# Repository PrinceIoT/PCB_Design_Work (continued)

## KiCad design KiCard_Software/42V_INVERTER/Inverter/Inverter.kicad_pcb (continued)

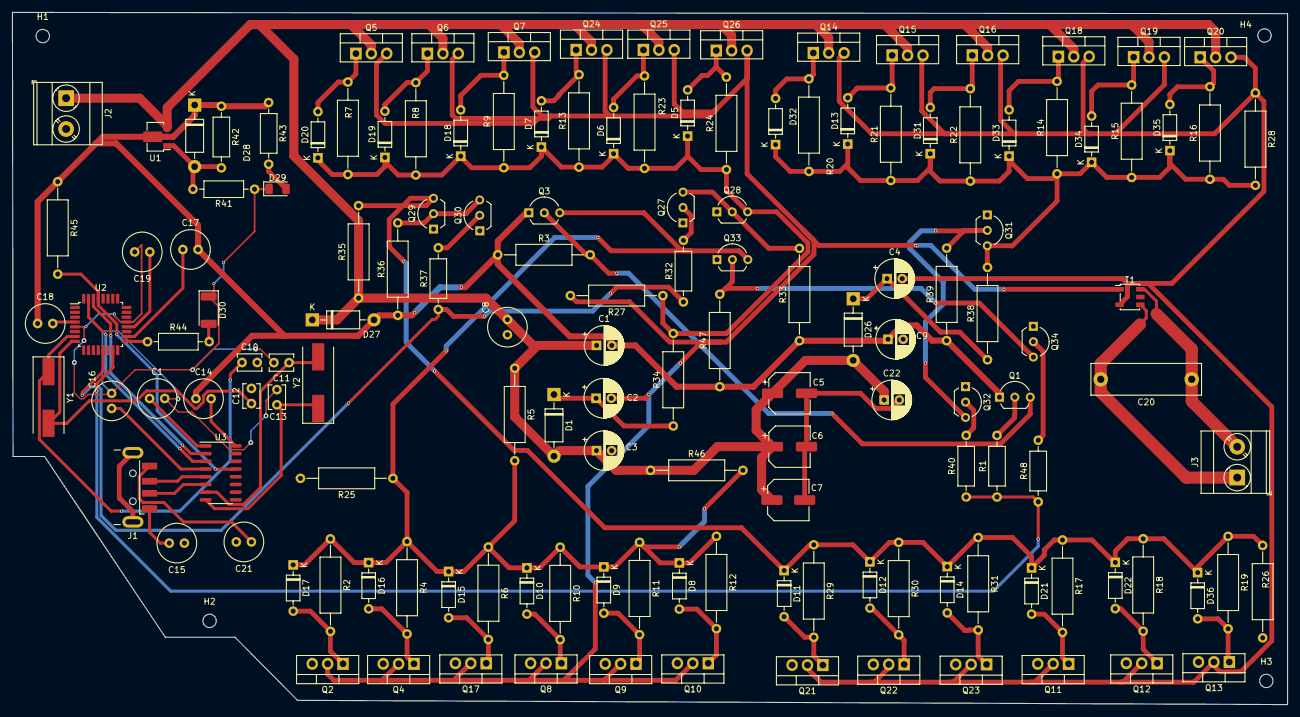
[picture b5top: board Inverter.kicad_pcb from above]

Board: 2 copper layers, 210.2 x 114.1 mm, 148 parts (0 on the bottom side), 70 nets.

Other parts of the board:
C1#2: 0.1uF; C_Radial_D6.3mm_H7.0mm_P2.50mm
Q1, Q3: 2N3904; TO-92_Inline_Wide
R1: 200; R_Axial_DIN0207_L6.3mm_D2.5mm_P10.16mm_Horizontal
R3: 10k; R_Axial_DIN0309_L9.0mm_D3.2mm_P15.24mm_Horizontal
R5: 20k; R_Axial_DIN0309_L9.0mm_D3.2mm_P15.24mm_Horizontal

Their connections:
11: R1.1; also elsewhere on the board
unnamed 9: Q3.3 (C), R5.2; also elsewhere on the board
unnamed: Q1.2 (B), R1.2
unnamed: Q1.3 (C), Q3.2 (B), R3.2

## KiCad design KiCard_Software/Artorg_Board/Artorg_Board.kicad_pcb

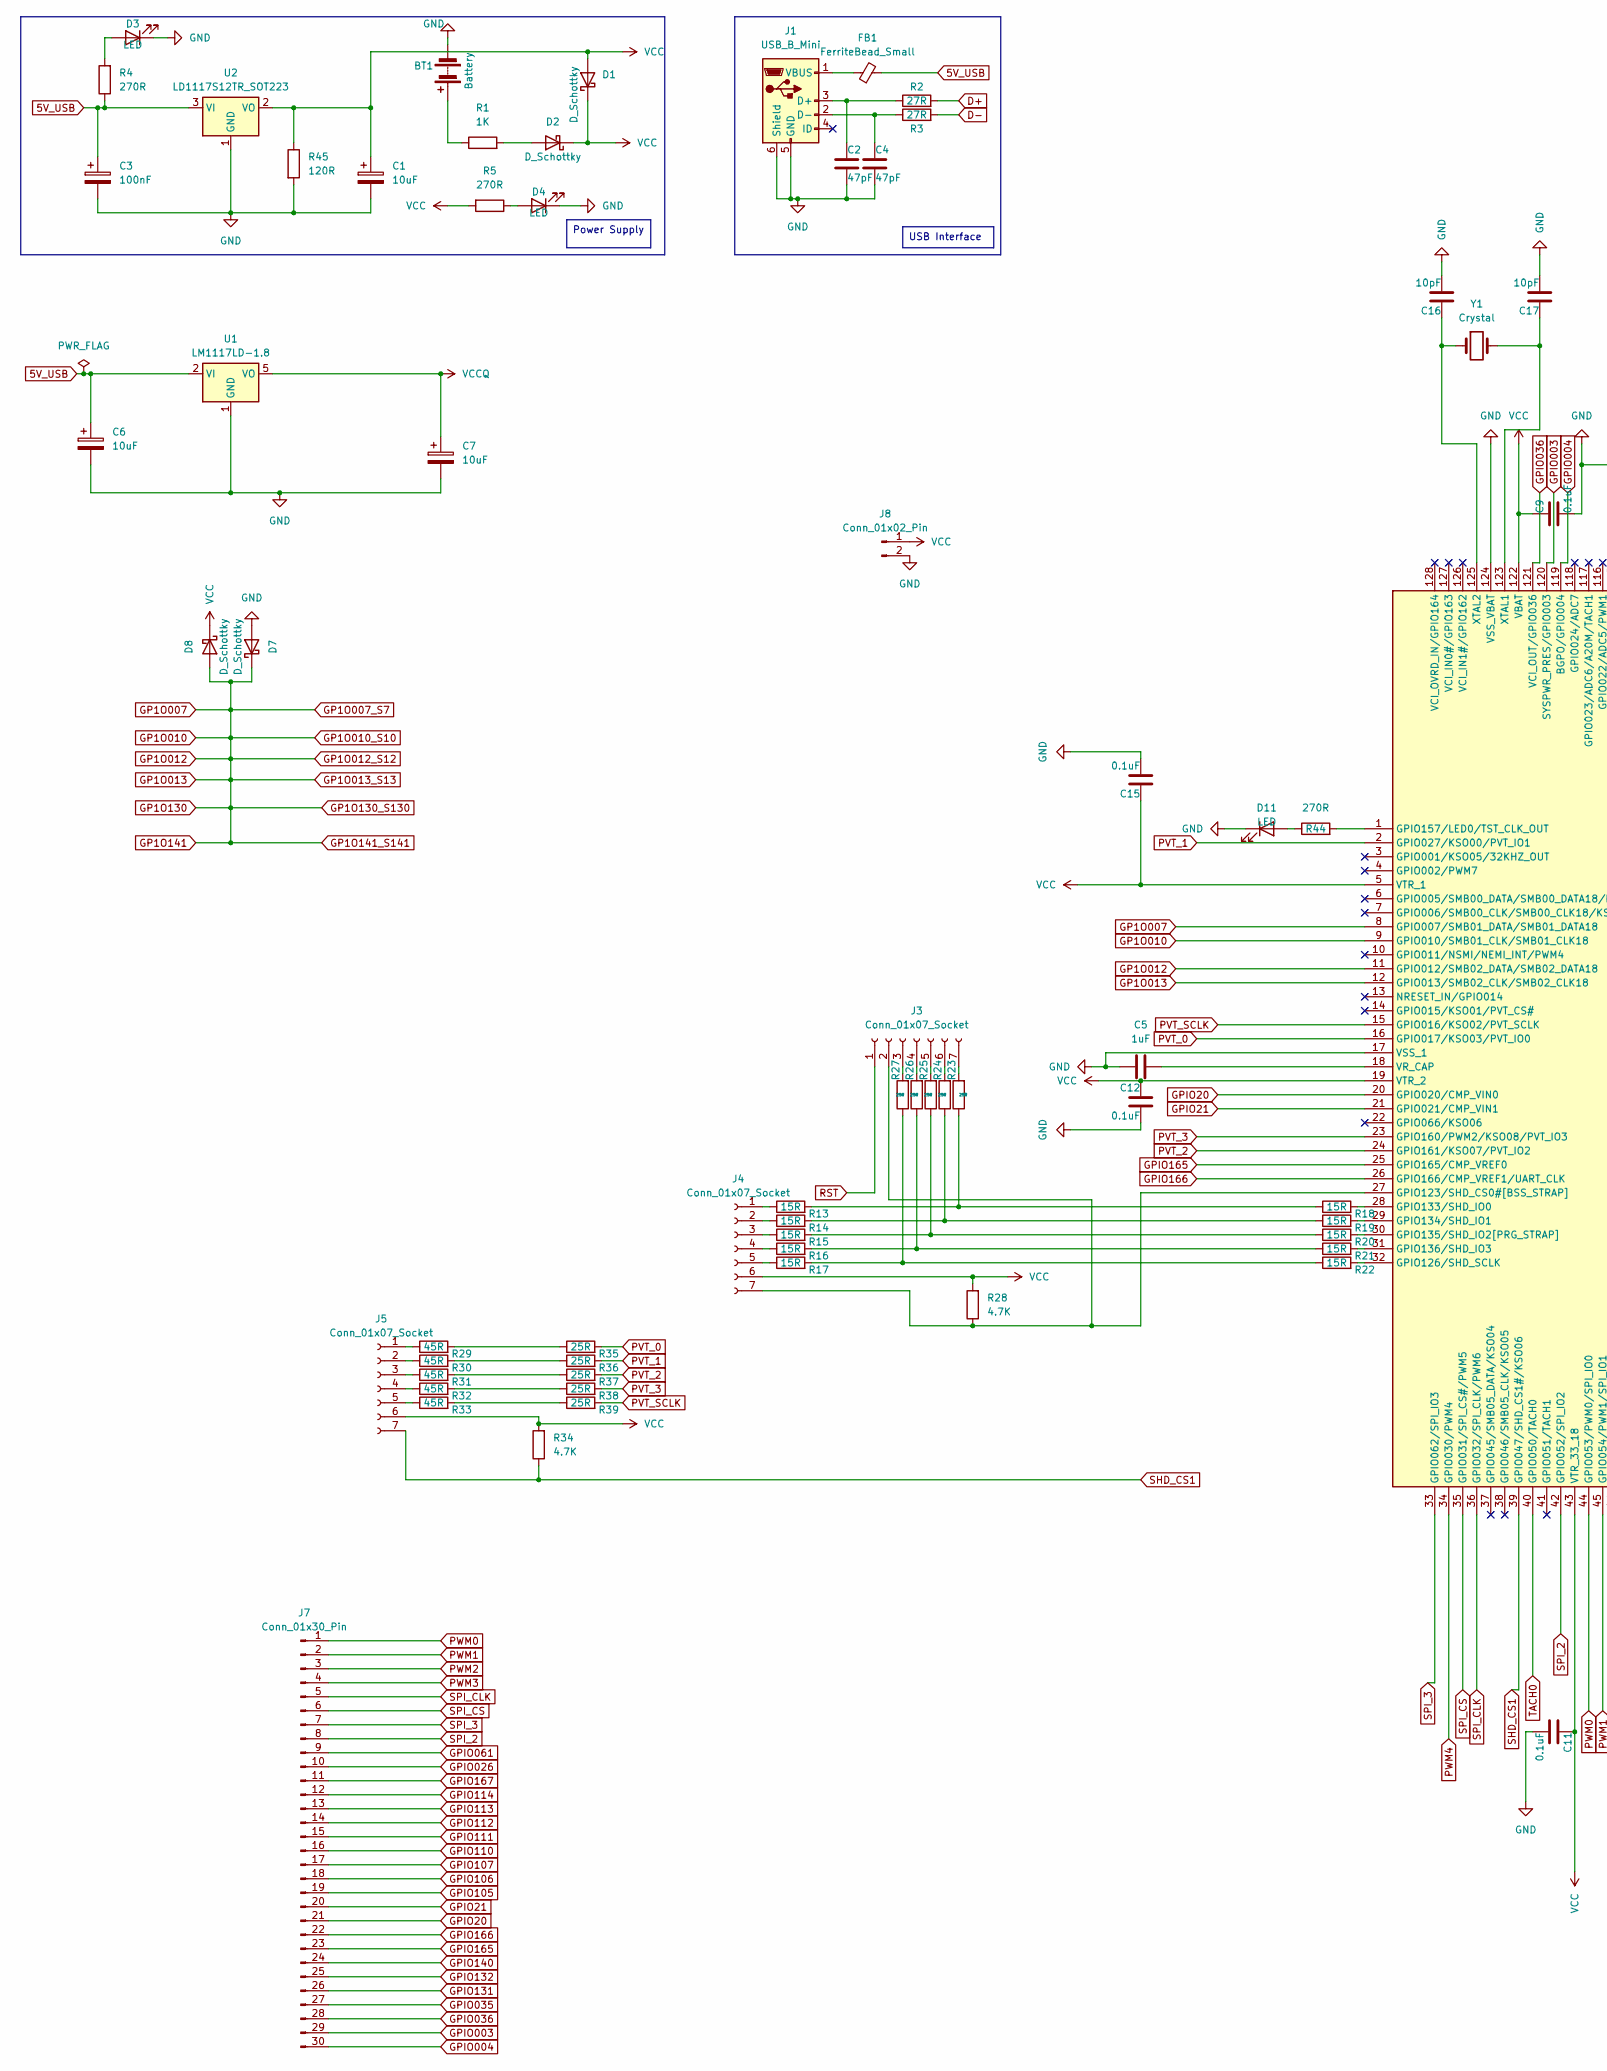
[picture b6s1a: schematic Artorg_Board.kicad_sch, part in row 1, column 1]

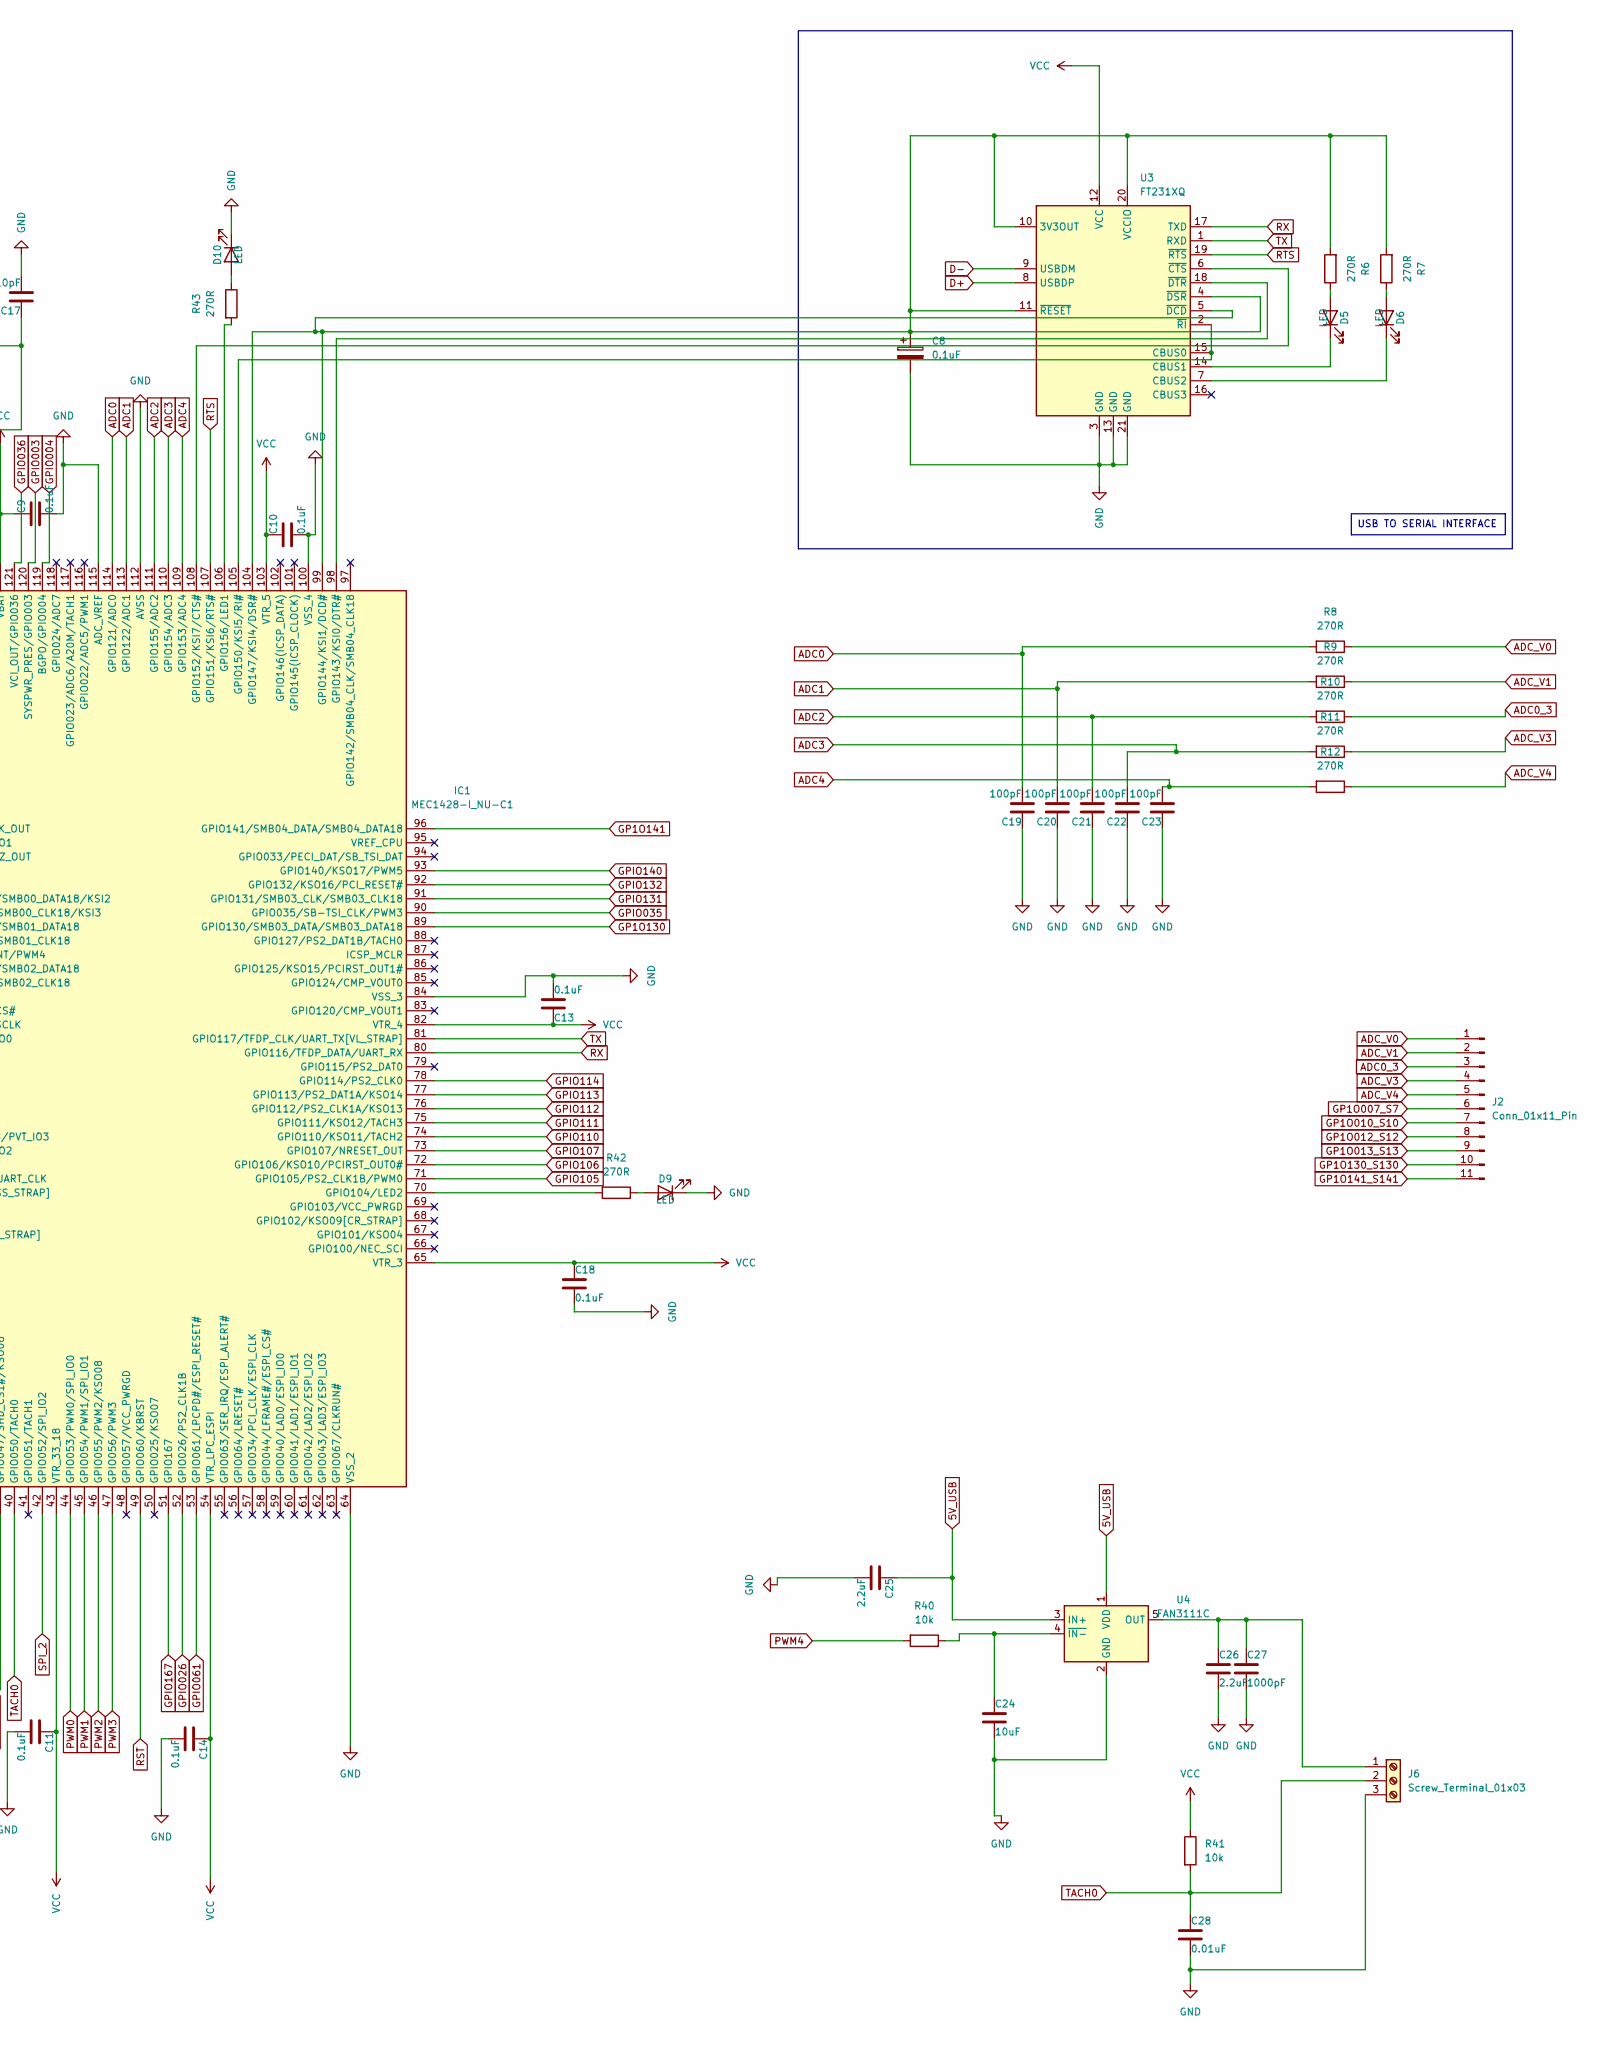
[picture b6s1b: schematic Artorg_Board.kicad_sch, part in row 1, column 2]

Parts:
BT1: Battery; BatteryHolder_Keystone_3000_1x12mm
C1, C6: 10uF; CP_Elec_4x4.5
C2, C4: 47pF; C_0805_2012Metric_Pad1.18x1.45mm_HandSolder
C3: 100nF; CP_Elec_3x5.3
C5: 1uF; C_0805_2012Metric_Pad1.18x1.45mm_HandSolder
C7: 10uF; CP_Elec_5x3.9
C8: 0.1uF; CP_EIA-7132-20_AVX-U_Pad2.72x3.50mm_HandSolder
C9, C10, C11, C12, C13, C14, C15: 0.1uF; C_0805_2012Metric_Pad1.18x1.45mm_HandSolder
C16, C17: 10pF; C_0805_2012Metric_Pad1.18x1.45mm_HandSolder
C18: 0.1uF; C_0603_1608Metric
C19, C20, C21, C22, C23: 100pF; C_0603_1608Metric
C24: 10uF; C_0805_2012Metric_Pad1.18x1.45mm_HandSolder
C25, C26: 2.2uF; C_0603_1608Metric_Pad1.08x0.95mm_HandSolder
C27: 1000pF; C_1206_3216Metric
C28: 0.01uF; C_1206_3216Metric_Pad1.33x1.80mm_HandSolder
D1, D2, D7, D8: D_Schottky; D_1210_3225Metric_Pad1.42x2.65mm_HandSolder
D3, D4, D5, D6, D9, D10, D11: LED; LED_1812_4532Metric
FB1: FerriteBead_Small; L_2010_5025Metric_Pad1.52x2.65mm_HandSolder
IC1: MEC1428-I_NU-C1; QFP40P1600X1600X120-128N; Mouser Part Number 579-MEC1428-I/NU-C1
J1: USB_B_Mini; USB_Micro-B_Amphenol_10118194_Horizontal
J2: Conn_01x11_Pin; Wago_734-141_1x11_P3.50mm_Vertical
J3, J4, J5: Conn_01x07_Socket; Wago_734-137_1x07_P3.50mm_Vertical
J6: Screw_Terminal_01x03; TerminalBlock_Altech_AK300-3_P5.00mm
J7: Conn_01x30_Pin; PinSocket_1x30_P1.27mm_Vertical_SMD_Pin1Left
J8: Conn_01x02_Pin; PinHeader_1x02_P1.00mm_Vertical_SMD_Pin1Right
R1: 1K; R_0805_2012Metric
R2, R3: 27R; R_0805_2012Metric
R4, R5, R6, R7, R8, R9, R10, R11, R12: 270R; R_0805_2012Metric
R13, R14, R15, R16, R17, R18, R19, R20, R21, R22: 15R; R_0805_2012Metric
R23, R24, R25, R26: 25R; R_0805_2012Metric
R27: 25R; R_0603_1608Metric_Pad0.98x0.95mm_HandSolder
R28, R34: 4.7K; R_0805_2012Metric_Pad1.20x1.40mm_HandSolder
R29, R30, R31, R32, R33: 45R; R_0805_2012Metric_Pad1.20x1.40mm_HandSolder
R35, R36, R37, R38, R39: 25R; R_0805_2012Metric_Pad1.20x1.40mm_HandSolder
R40, R41: 10k; R_0805_2012Metric_Pad1.20x1.40mm_HandSolder
R42, R43, R44: 270R; R_0805_2012Metric_Pad1.20x1.40mm_HandSolder
R45: 120R; R_0805_2012Metric
U1: LM1117LD-1.8; WSON-8-1EP_4x4mm_P0.8mm_EP2.2x3mm
U2: LD1117S12TR_SOT223; SOT-223-3_TabPin2
U3: FT231XQ; QFN-20-1EP_4x4mm_P0.5mm_EP2.5x2.5mm
U4: FAN3111C; SOT-23-5
Y1: Crystal; Crystal_SMD_0603-2Pin_6.0x3.5mm_HandSoldering

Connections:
5V_USB: C3.1, C6.1, C25.1, FB1.2, R4.1, U1.2 (VI), U1.3 (VI), U1.4 (VI), U2.3 (VI), U4.1 (VDD), U4.3 (IN+)
ADC0: C19.2, IC1.114 (GPIO121/ADC0), R8.2
ADC0_3: J2.3, R10.1
ADC1: C20.2, IC1.113 (GPIO122/ADC1), R9.2
ADC2: C21.2, IC1.111 (GPIO155/ADC2), R10.2
ADC3: C22.2, IC1.110 (GPIO154/ADC3), R11.2
ADC4: C23.2, IC1.109 (GPIO153/ADC4), R12.2
ADC_V0: J2.1, R8.1
ADC_V1: J2.2, R9.1
ADC_V3: J2.4, R11.1
ADC_V4: J2.5, R12.1
D+: R2.2, U3.8 (USBDP)
D-: R3.2, U3.9 (USBDM)
GND: BT1.2 (-), C1.2, C2.2, C3.2, C4.2, C5.1, C6.2, C7.2, C8.2, C9.2, C10.2, C11.2, C12.2, C13.2, C14.2, C15.2, C16.2, C17.2, C18.2, C19.1, C20.1, C21.1, C22.1, C23.1, C24.2, C25.2, C26.2, C27.2, C28.2, D3.1 (K), D4.1 (K), D7.2 (A), D9.1 (K), D10.1 (K), D11.1 (K), IC1.17 (VSS_1), IC1.64 (VSS_2), IC1.84 (VSS_3), IC1.100 (VSS_4), IC1.112 (AVSS), IC1.115 (ADC_VREF), IC1.124 (VSS_VBAT), J1.5 (GND), J1.6 (Shield), J6.3, J8.2, R45.2, U1.1 (GND), U2.1 (GND), U3.3 (GND), U3.13 (GND), U3.21 (GND), U4.2 (GND)
GP1O007: D7.1 (K), D8.2 (A), IC1.8 (GPIO007/SMB01_DATA/SMB01_DATA18), IC1.9 (GPIO010/SMB01_CLK/SMB01_CLK18), IC1.11 (GPIO012/SMB02_DATA/SMB02_DATA18), IC1.12 (GPIO013/SMB02_CLK/SMB02_CLK18), IC1.89 (GPIO130/SMB03_DATA/SMB03_DATA18), IC1.96 (GPIO141/SMB04_DATA/SMB04_DATA18), J2.6, J2.7, J2.8, J2.9, J2.10, J2.11
GPIO003: IC1.120 (SYSPWR_PRES/GPIO003), J7.29
GPIO004: IC1.119 (BGPO/GPIO004), J7.30
GPIO20: IC1.20 (GPIO020/CMP_VIN0), J7.21
GPIO21: IC1.21 (GPIO021/CMP_VIN1), J7.20
GPIO026: IC1.52 (GPIO026/PS2_CLK1B), J7.10
GPIO035: IC1.90 (GPIO035/SB-TSI_CLK/PWM3), J7.27
GPIO036: IC1.121 (VCI_OUT/GPIO036), J7.28
GPIO061: IC1.53 (GPIO061/LPCPD#/ESPI_RESET#), J7.9
GPIO105: IC1.71 (GPIO105/PS2_CLK1B/PWM0), J7.19
GPIO106: IC1.72 (GPIO106/KSO10/PCIRST_OUT0#), J7.18
GPIO107: IC1.73 (GPIO107/NRESET_OUT), J7.17
GPIO110: IC1.74 (GPIO110/KSO11/TACH2), J7.16
GPIO111: IC1.75 (GPIO111/KSO12/TACH3), J7.15
GPIO112: IC1.76 (GPIO112/PS2_CLK1A/KSO13), J7.14
GPIO113: IC1.77 (GPIO113/PS2_DAT1A/KSO14), J7.13
GPIO114: IC1.78 (GPIO114/PS2_CLK0), J7.12
GPIO131: IC1.91 (GPIO131/SMB03_CLK/SMB03_CLK18), J7.26
GPIO132: IC1.92 (GPIO132/KSO16/PCI_RESET#), J7.25
GPIO140: IC1.93 (GPIO140/KSO17/PWM5), J7.24
GPIO165: IC1.25 (GPIO165/CMP_VREF0), J7.23
GPIO166: IC1.26 (GPIO166/CMP_VREF1/UART_CLK), J7.22
GPIO167: IC1.51 (GPIO167), J7.11
unnamed: BT1.1 (+), R1.1
unnamed: D2.2 (A), R1.2
unnamed: D3.2 (A), R4.2
unnamed: D4.2 (A), R5.1
unnamed: D5.2 (A), R6.1
unnamed: D5.1 (K), U3.14 (CBUS1)
unnamed: D6.2 (A), R7.1
unnamed: D6.1 (K), U3.7 (CBUS2)
unnamed: D9.2 (A), R42.1
unnamed: D10.2 (A), R43.1
unnamed: D11.2 (A), R44.1
unnamed: IC1.70 (GPIO104/LED2), R42.2
unnamed: IC1.27 (GPIO123/SHD_CS0#[BSS_STRAP]), J3.2, J4.7, R28.1
unnamed: IC1.32 (GPIO126/SHD_SCLK), R22.2
unnamed: IC1.28 (GPIO133/SHD_IO0), R18.2
unnamed: IC1.29 (GPIO134/SHD_IO1), R19.2
unnamed: IC1.30 (GPIO135/SHD_IO2[PRG_STRAP]), R20.2
unnamed: IC1.31 (GPIO136/SHD_IO3), R21.2
unnamed: IC1.98 (GPIO143/KSI0/DTR#), U3.18 (~DTR)
unnamed: C8.1, IC1.99 (GPIO144/KSI1/DCD#), IC1.104 (GPIO147/KSI4/DSR#), R6.2, R7.2, U3.4 (~DSR), U3.5 (~DCD), U3.10 (3V3OUT), U3.11 (~RESET), U3.20 (VCCIO)
unnamed: IC1.105 (GPIO150/KSI5/RI#), U3.2 (~RI), U3.15 (CBUS0)
unnamed: IC1.107 (GPIO151/KSI6/RTS#), U3.19 (~RTS)
unnamed: IC1.108 (GPIO152/KSI7/CTS#), U3.6 (~CTS)
unnamed: IC1.106 (GPIO156/LED1), R43.2
unnamed: IC1.1 (GPIO157/LED0/TST_CLK_OUT), R44.2
unnamed: C5.2, IC1.18 (VR_CAP)
unnamed: C17.1, IC1.123 (XTAL1), Y1.2
unnamed: C16.1, IC1.125 (XTAL2), Y1.1
unnamed: C2.1, J1.3 (D+), R2.1
unnamed: C4.1, J1.2 (D-), R3.1
unnamed: FB1.1, J1.1 (VBUS)
unnamed: J3.3, R27.2
unnamed: J3.4, R26.2
unnamed: J3.5, R25.2
unnamed: J3.6, R24.2
unnamed: J3.7, R23.2
unnamed: J4.1, R13.1
unnamed: J4.2, R14.1
unnamed: J4.3, R15.1
unnamed: J4.4, R16.1
unnamed: J4.5, R17.1
unnamed: J5.1, R29.1
unnamed: J5.2, R30.1
unnamed: J5.3, R31.1
unnamed: J5.4, R32.1
unnamed: J5.5, R33.1
unnamed: C26.1, C27.1, J6.1, U4.5 (OUT)
unnamed: R13.2, R18.1, R23.1
unnamed: R14.2, R19.1, R24.1
unnamed: R15.2, R20.1, R25.1
unnamed: R16.2, R21.1, R26.1
unnamed: R17.2, R22.1, R27.1
unnamed: R29.2, R35.1
unnamed: R30.2, R36.1
unnamed: R31.2, R37.1
unnamed: R32.2, R38.1
unnamed: R33.2, R39.1
unnamed: C24.1, R40.1, U4.4 (~IN-)
PVT_0: IC1.16 (GPIO017/KSO03/PVT_IO0), R35.2
PVT_1: IC1.2 (GPIO027/KSO00/PVT_IO1), R36.2
PVT_2: IC1.24 (GPIO161/KSO07/PVT_IO2), R37.2
PVT_3: IC1.23 (GPIO160/PWM2/KSO08/PVT_IO3), R38.2
PVT_SCLK: IC1.15 (GPIO016/KSO02/PVT_SCLK), R39.2
PWM0: IC1.44 (GPIO053/PWM0/SPI_IO0), J7.1
PWM1: IC1.45 (GPIO054/PWM1/SPI_IO1), J7.2
PWM2: IC1.46 (GPIO055/PWM2/KSO08), J7.3
PWM3: IC1.47 (GPIO056/PWM3), J7.4
PWM4: IC1.34 (GPIO030/PWM4), R40.2
RST: IC1.49 (GPIO060/KBRST), J3.1
RX: IC1.80 (GPIO116/TFDP_DATA/UART_RX), U3.17 (TXD)
SHD_CS1: IC1.39 (GPIO047/SHD_CS1#/KSO06), J5.7, R34.1
SPI_2: IC1.42 (GPIO052/SPI_IO2), J7.8
SPI_3: IC1.33 (GPIO062/SPI_IO3), J7.7
SPI_CLK: IC1.36 (GPIO032/SPI_CLK/PWM6), J7.5
SPI_CS: IC1.35 (GPIO031/SPI_CS#/PWM5), J7.6
TACH0: C28.1, IC1.40 (GPIO050/TACH0), J6.2, R41.2
TX: IC1.81 (GPIO117/TFDP_CLK/UART_TX[VL_STRAP]), U3.1 (RXD)
VCC: C1.1, C9.1, C10.1, C11.1, C12.1, C13.1, C14.1, C15.1, C18.1, D1.1 (K), D1.2 (A), D2.1 (K), D8.1 (K), IC1.5 (VTR_1), IC1.19 (VTR_2), IC1.43 (VTR_33_18), IC1.54 (VTR_LPC_ESPI), IC1.65 (VTR_3), IC1.82 (VTR_4), IC1.103 (VTR_5), IC1.122 (VBAT), J4.6, J5.6, J8.1, R5.2, R28.2, R34.2, R41.1, R45.1, U2.2 (VO), U3.12 (VCC)
VCCQ: C7.1, U1.5 (VO), U1.6 (VO), U1.7 (VO), U1.9 (VO)

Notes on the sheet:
USB Interface
USB TO SERIAL INTERFACE
Power Supply

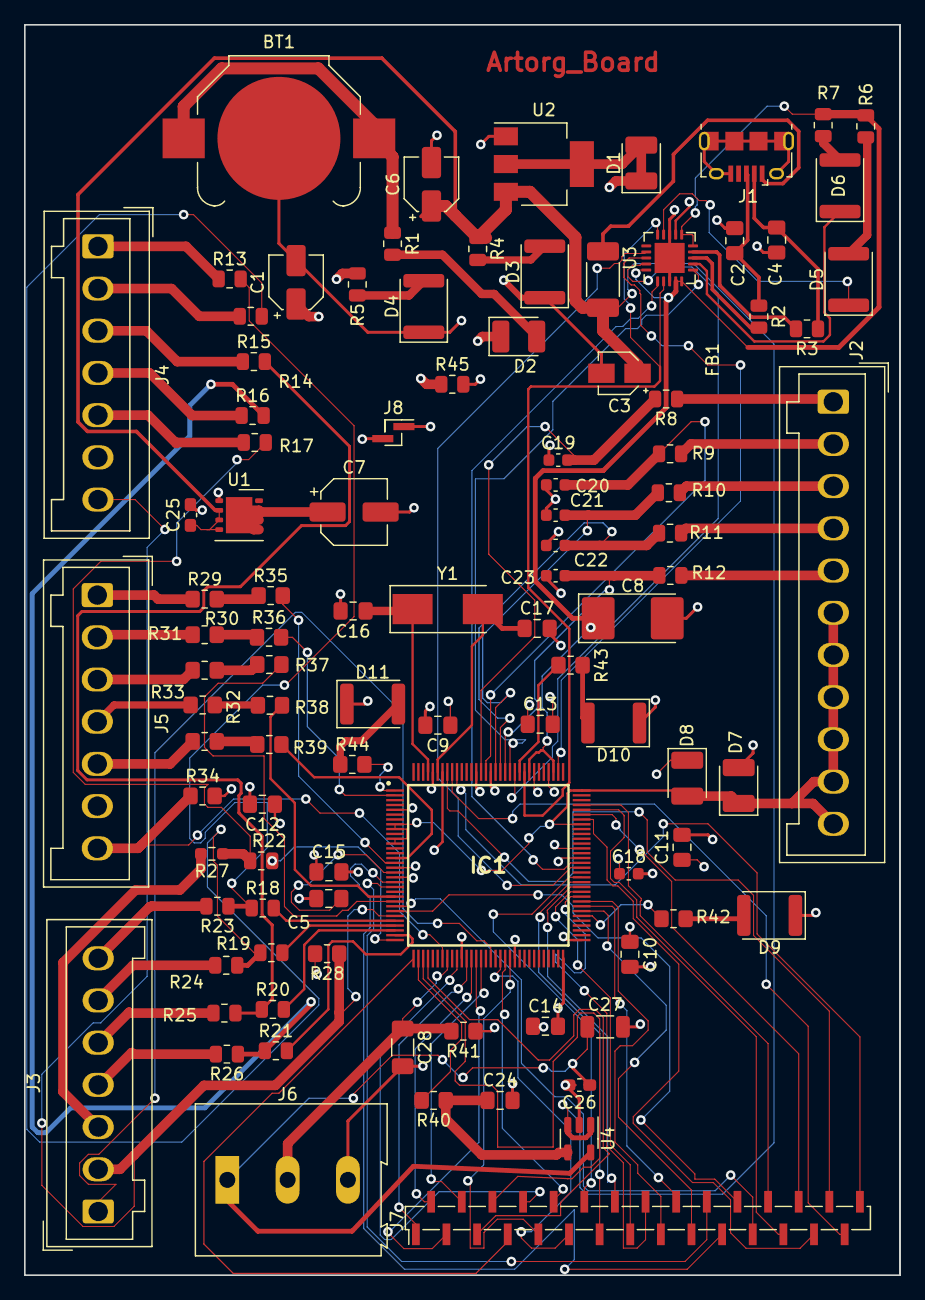
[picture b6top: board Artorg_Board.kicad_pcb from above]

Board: 4 copper layers, 72.6 x 103.7 mm, 100 parts (0 on the bottom side), 116 nets.

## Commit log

2024-11-11 PCB design
